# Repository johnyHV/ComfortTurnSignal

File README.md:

# ComfortTurnSignal

This project is default use for VW Golf MK4 comfort turn signal. 
Schematic and source code it can also be used in another car without comfort turn signal.

Youtube video

# Change log

Version 1.2.1
- HW version 1.2
- SW version 1.4.1

Version 1.2
- HW version 1.2
- SW version 1.4.0

Version 1.1
- HW version 1.1
- SW version 1.3

# Change log SW

Version 1.4.1
- added function, for change blink interval, if is jumper set. Function for this featchure is CheckBlinkIntervalJumper. But if is this function enabled in main.c, then must be definition EEPROM_ENABLE set to 0

Version 1.4.0
- added conf.h file with global MCU configuration
- added debounce time for self calibration SET jumper

Version 1.3.0
- added featchure for disable trippling, when pressing the turn signal control for the opposite direction of flashing

Version 1.2.0
- added fix time for blinking from FLASH memmory

Version 1.1
- Fix bug

Version 1.0
- Init version

# Change log HW

Version 1.2
- update MCU connection
- added SPI programming connector
- added 100nF capacitor for MCU
- added description on the PCB

Version 1.1
- fixed problem with PCB design

Version 1.0
- first version

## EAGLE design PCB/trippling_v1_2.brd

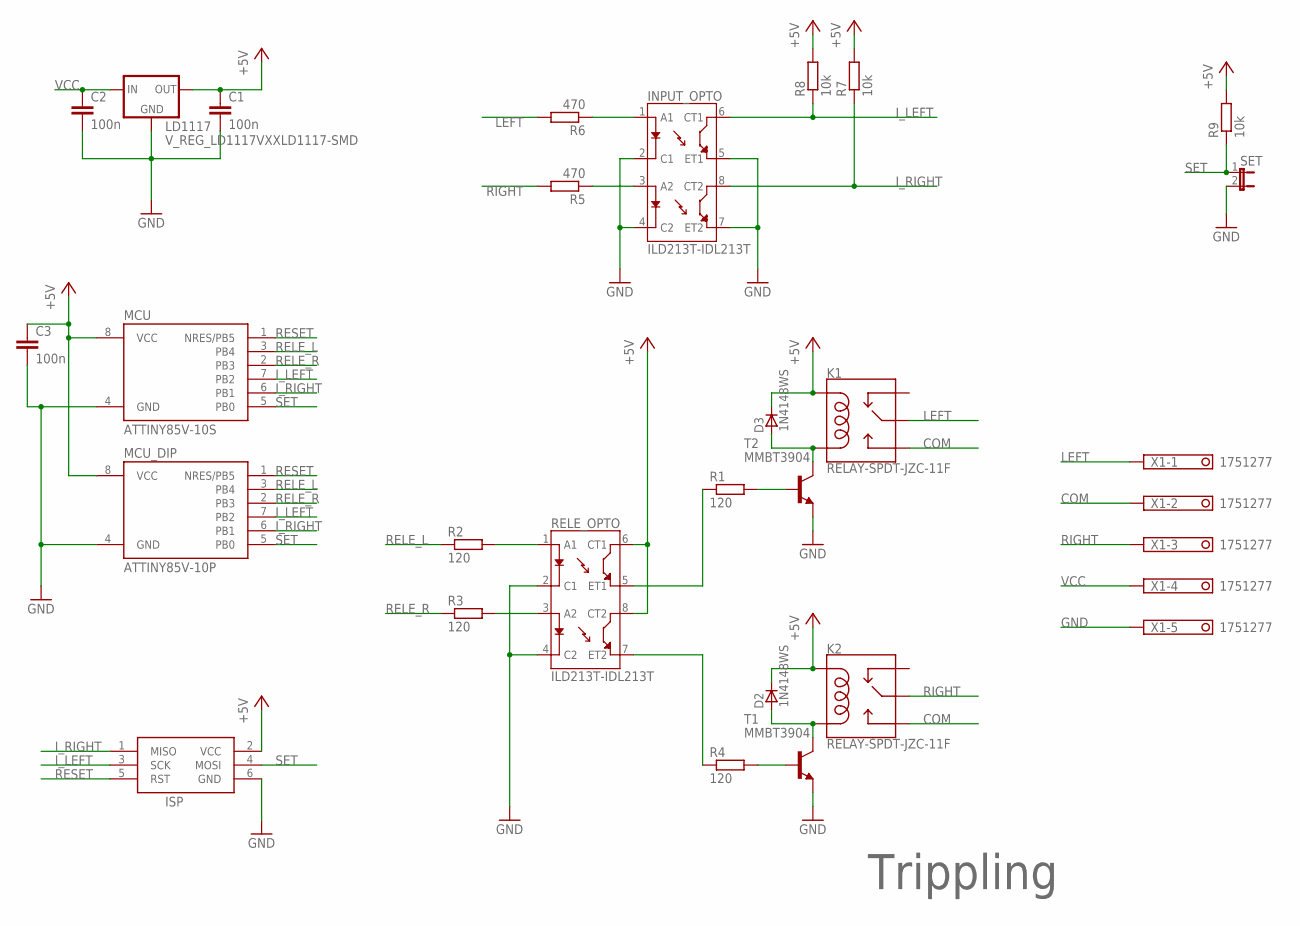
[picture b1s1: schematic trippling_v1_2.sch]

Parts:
C1, C2, C3: 100n; C0805
D2, D3: 1N4148WS; SOD323F
INPUT_OPTO: ILD213T-IDL213T; SO08
ISP: AVRISP-6; AVRISP
K1, K2: RELAY-SPDT-JZC-11F; RELAY-JZC
LD1117: V_REG_LD1117VXXLD1117-SMD; SOT223
MCU: ATTINY85V-10S; SOIC8_EIAJ_208MIL
MCU_DIP: ATTINY85V-10P; PDIP08_300MIL
R1, R2, R3, R4: 120; R0805
R5, R6: 470; R0805
R7, R8, R9: 10k; R0805
RELE_OPTO: ILD213T-IDL213T; SO08
SET: JP1E; JP1
T1, T2: MMBT3904; SOT23-BEC
X1: 1751277

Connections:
+5V: C1.1, C3.1, D2.C, D3.C, ISP.2 (VCC), K1.5 (COIL1), K2.5 (COIL1), LD1117.2 (OUT), MCU.8 (VCC), MCU_DIP.8 (VCC), R7.2, R8.2, R9.2, RELE_OPTO.6 (CT1), RELE_OPTO.8 (CT2)
COM: K1.3 (NO), K2.3 (NO), X1.2
GND: C1.2, C2.2, C3.2, INPUT_OPTO.2 (C1), INPUT_OPTO.4 (C2), INPUT_OPTO.5 (ET1), INPUT_OPTO.7 (ET2), ISP.6 (GND), LD1117.1 (GND), MCU.4 (GND), MCU_DIP.4 (GND), RELE_OPTO.2 (C1), RELE_OPTO.4 (C2), SET.2, T1.E, T2.E, X1.5
I_LEFT: INPUT_OPTO.6 (CT1), ISP.3 (SCK), MCU.7 (PB2), MCU_DIP.7 (PB2), R8.1
I_RIGHT: INPUT_OPTO.8 (CT2), ISP.1 (MISO), MCU.6 (PB1), MCU_DIP.6 (PB1), R7.1
LEFT: K1.4 (MAIN), R6.2, X1.1
unnamed: INPUT_OPTO.1 (A1), R6.1
unnamed: INPUT_OPTO.3 (A2), R5.1
unnamed: D3.A, K1.1 (COIL2), T2.C
unnamed: R1.2, T2.B
unnamed: R4.2, T1.B
unnamed: D2.A, K2.1 (COIL2), T1.C
unnamed: R1.1, RELE_OPTO.5 (ET1)
unnamed: R4.1, RELE_OPTO.7 (ET2)
unnamed: R3.2, RELE_OPTO.3 (A2)
unnamed: R2.2, RELE_OPTO.1 (A1)
RELE_L: MCU.3 (PB4), MCU_DIP.3 (PB4), R2.1
RELE_R: MCU.2 (PB3), MCU_DIP.2 (PB3), R3.1
RESET: ISP.5 (RST), MCU.1 (NRES/PB5), MCU_DIP.1 (NRES/PB5)
RIGHT: K2.4 (MAIN), R5.2, X1.3
SET: ISP.4 (MOSI), MCU.5 (PB0), MCU_DIP.5 (PB0), R9.1, SET.1
VCC: C2.1, LD1117.3 (IN), X1.4

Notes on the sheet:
Trippling

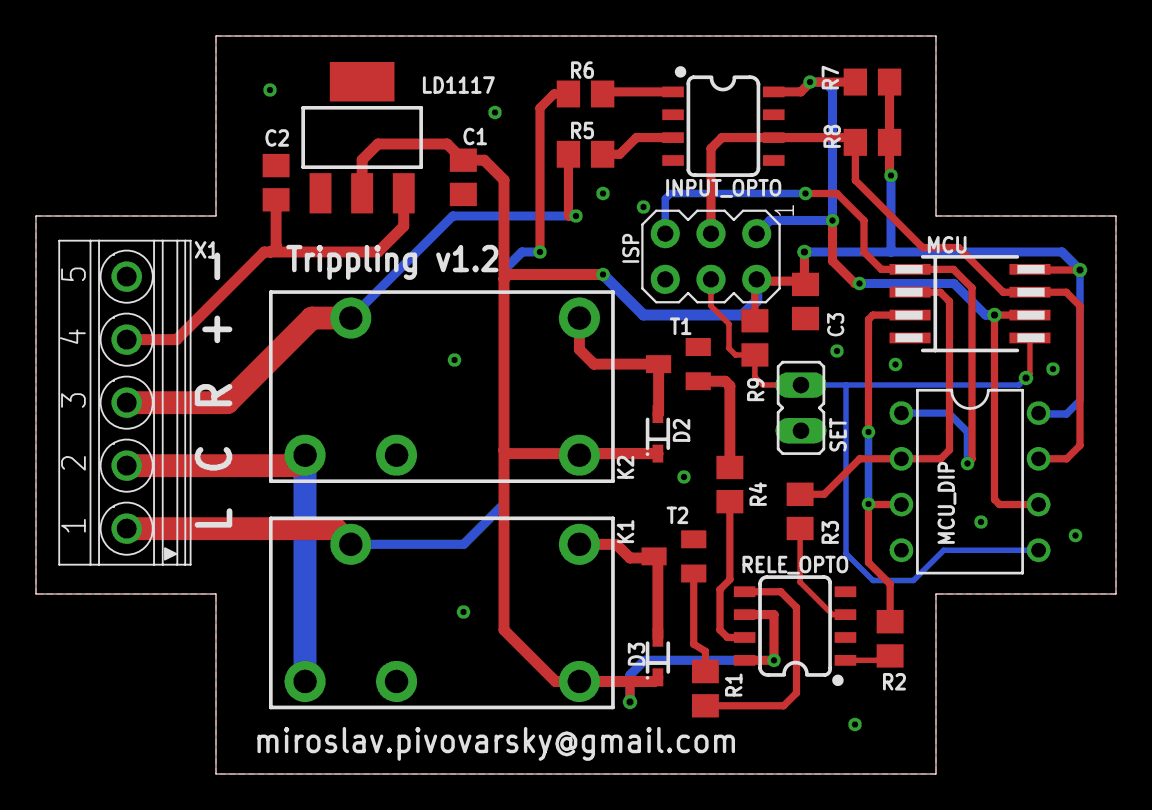
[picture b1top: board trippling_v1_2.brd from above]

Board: 2 copper layers, 60.0 x 41.0 mm, 26 parts (0 on the bottom side), 22 nets.

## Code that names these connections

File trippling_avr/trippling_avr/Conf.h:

/*
 * Conf.h
 *
 * Created: 15. 10. 2020 8:21:08
 *  @author Miroslav Pivovarsky (mpivovarsky)
 *  @version 0.1
 *  @bug No know bugs.
 *
 */ 

#ifndef CONF_H_
#define CONF_H_

#include <avr/io.h>

#define SOFTWARE_VERSION		"1.4.1"	///< Software version
#define HARDWARE_VERSION		12		///< hardware version 1.1 or 1.2

#define F_CPU 8000000					///< 8.0Mhz/8 = 1.0Mhz

#if (HARDWARE_VERSION == 12)
#define INPUT_LEFT				PB2		///< LEFT input
#define INPUT_RIGHT				PB1		///< RIGHT input
#define INPUT_SET_BUTTON		PB0		///< configuration button input
#define RELE_LEFT				PB4		///< LEFT rele
#define RELE_RIGHT				PB3		///< RIGHT rele
#endif

#if (HARDWARE_VERSION == 11)
#define INPUT_LEFT				PB4		///< LEFT input
#define INPUT_RIGHT				PB3		///< RIGHT input
#define INPUT_SET_BUTTON		PB0		///< configuration button input
#define RELE_LEFT				PB2		///< LEFT rele
#define RELE_RIGHT				PB1		///< RIGHT rele
#endif

#define EEPROM_ENABLE			0		///< Enable/disable EEPROM memmory
#define EEPROM_TIME_FLASHING	0x00	///< EEPROM address for store uint16 value for time BULB ON and OFF
#define BLINK_INTERVAL			3		///< triple flash interval
#define REFRESH_TIME			5		///< Refres time for super loop
#define SAFETY_DELAY			500		///< Safety timer
#define TIME_ON_OFF_LENGTH		400		///< timer for length bulb on and off
#define TIMEOUT_ENABLE_BULB		300		///< timeout for enable turn ON bulb
#define MIN_TIME_FOR_EN_TRIPP	80		///< Minimum time for enable trippling

#define TRUE 1							///< True value
#define FALSE 0							///< False value
#define BULB_ON TRUE					///< Bulb on value
#define BULB_OFF FALSE					///< Bulb off value

#endif /* CONF_H_ */

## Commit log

2018-11-15 Add source code documentation Add mode for learning time to blinking bulb
2019-11-18 Fix HW pinout Fix SW pinout add documentation for AVR dragon
2020-10-26 [PCB]
    - update original PCB
2020-10-26 [PCB]
    - add version 1.2
    - update MCU connection
    - add SPI programming connector
    - add 100nF capacitor for MCU
    - add description
2020-10-26 [SW]
    - update SW for PCB version 1.2
    - fix typo
    - create Conf.h for MCU global configuration
2020-10-26 [bin]
    - add HEX and SREC binary file
2020-10-26 [docu]
    - add documentation [SK language]
2020-10-31 [SW]
    - added function, for change blink interval, if is jumper set. Function for this featchure is CheckBlinkIntervalJumper. But if is this function enabled in main.c, then must be definition EEPROM_ENABL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

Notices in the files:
parts and their libraries:
SparkFun-Electromechanical: Licensing: Creative Commons ShareAlike 4.0 International - https://creativecommons.org/licenses/by-sa/4.0
